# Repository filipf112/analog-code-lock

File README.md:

# Analog code lock project
Project of analog code lock with circuit and PCB design

## System assumptions and operation
The project's assumption was to construct an analog code lock. The circuit was based on the digital circuit CD4017, which operates by changing the output after each pulse at the CLK input. Eight buttons were used to create a sequence forming a password, four of which were responsible for the password, while the rest reset the circuit upon being pressed. Pressing the correct buttons in the established order activates the LED and relay RY1. To secure the circuit, diodes and resistors were used, and capacitors were installed to stabilize the current flowing in the circuit.

## Schematic
Below is the schematic of the project created in the Eagle program, along with the names and values of the components.

## Simulation
To conduct the simulation, the SimulIDE program was used. As seen, upon pressing all the buttons forming the password in the correct sequence, the LED lights up, and the relay begins to operate.

## PCB Design
Based on the schematic created in the Eagle program, the PCB layout was generated.

## Final project

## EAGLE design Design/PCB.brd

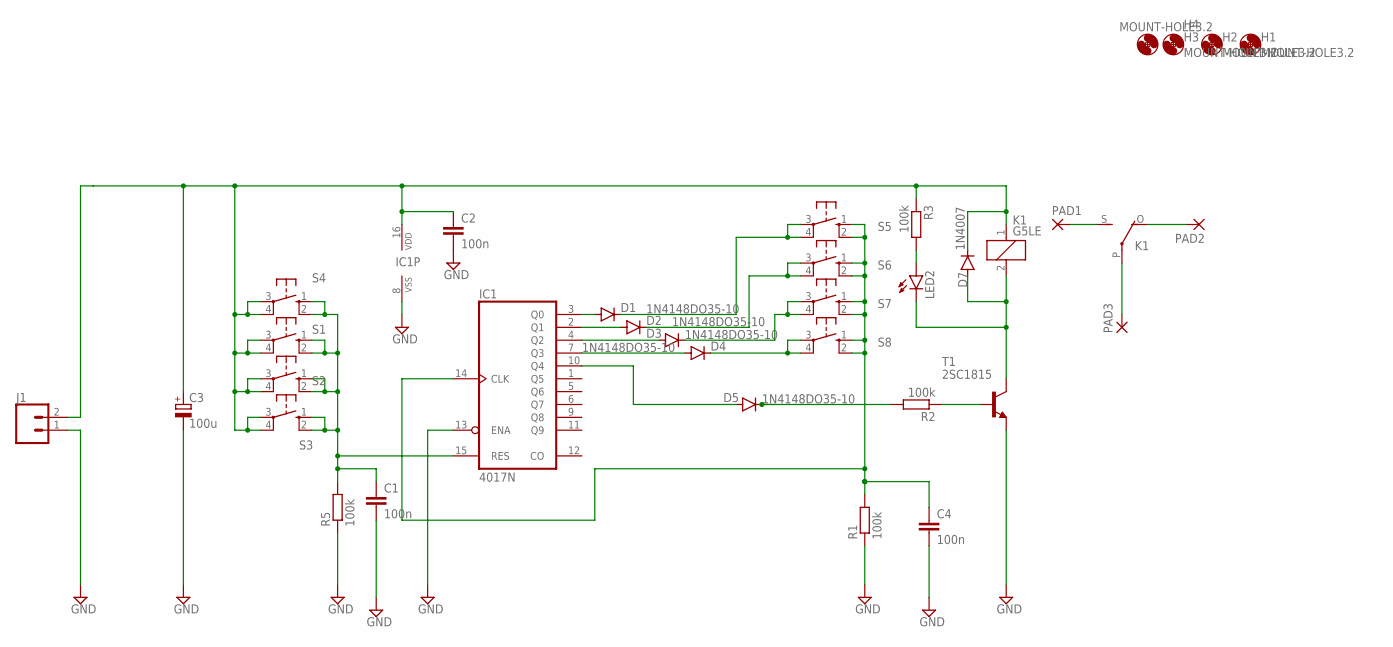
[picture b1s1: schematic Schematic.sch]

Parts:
C1, C2, C4: 100n; C025-060X050
C3: 100u; E2,5-6
D1, D2, D3, D4, D5: 1N4148DO35-10; DO35-10
D7: 1N4007; DO-41
H1, H2, H3, H4: MOUNT-HOLE3.2; 3,2
IC1: 4017N; DIL16
J1: CONN_023.5MM; SCREWTERMINAL-3.5MM-2
K1: G5LE
LED2: LED5MM
PAD1, PAD2, PAD3: 3,81/1,4
R1, R2, R3, R5: 100k; 0207/12
S1, S2, S3, S4, S5, S6, S7, S8: 10-XX; B3F-10XX
T1: 2SC1815; TO92-ECB

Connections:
GND: C1.2, C2.2, C3.-, C4.2, IC1.8 (VSS), IC1.13 (ENA), J1.1, R1.1, R5.1, T1.E
unnamed: C1.1, IC1.15 (RES), R5.2, S1.1 (S), S1.2 (S1), S2.1 (S), S2.2 (S1), S3.1 (S), S3.2 (S1), S4.1 (S), S4.2 (S1)
unnamed: D4.C, S8.3, S8.4 (P1)
unnamed: D4.A, IC1.7 (Q3)
unnamed: D3.A, IC1.4 (Q2)
unnamed: D2.A, IC1.2 (Q1)
unnamed: D1.A, IC1.3 (Q0)
unnamed: D3.C, S7.3, S7.4 (P1)
unnamed: D2.C, S6.3, S6.4 (P1)
unnamed: C4.1, IC1.14 (CLK), R1.2, S5.1 (S), S5.2 (S1), S6.1 (S), S6.2 (S1), S7.1 (S), S7.2 (S1), S8.1 (S), S8.2 (S1)
unnamed: D1.C, S5.3, S5.4 (P1)
unnamed: K1.S, PAD1.1
unnamed: D5.A, IC1.10 (Q4)
unnamed: K1.O, PAD2.1
unnamed: D7.A, K1.2, LED2.K (C), T1.C
unnamed: D5.C, R2.2
unnamed: R2.1, T1.B
unnamed: LED2.A, R3.2
unnamed: K1.P, PAD3.1
unnamed: C2.1, C3.+, D7.C, IC1.16 (VDD), J1.2, K1.1, R3.1, S1.3, S1.4 (P1), S2.3, S2.4 (P1), S3.3, S3.4 (P1), S4.3, S4.4 (P1)

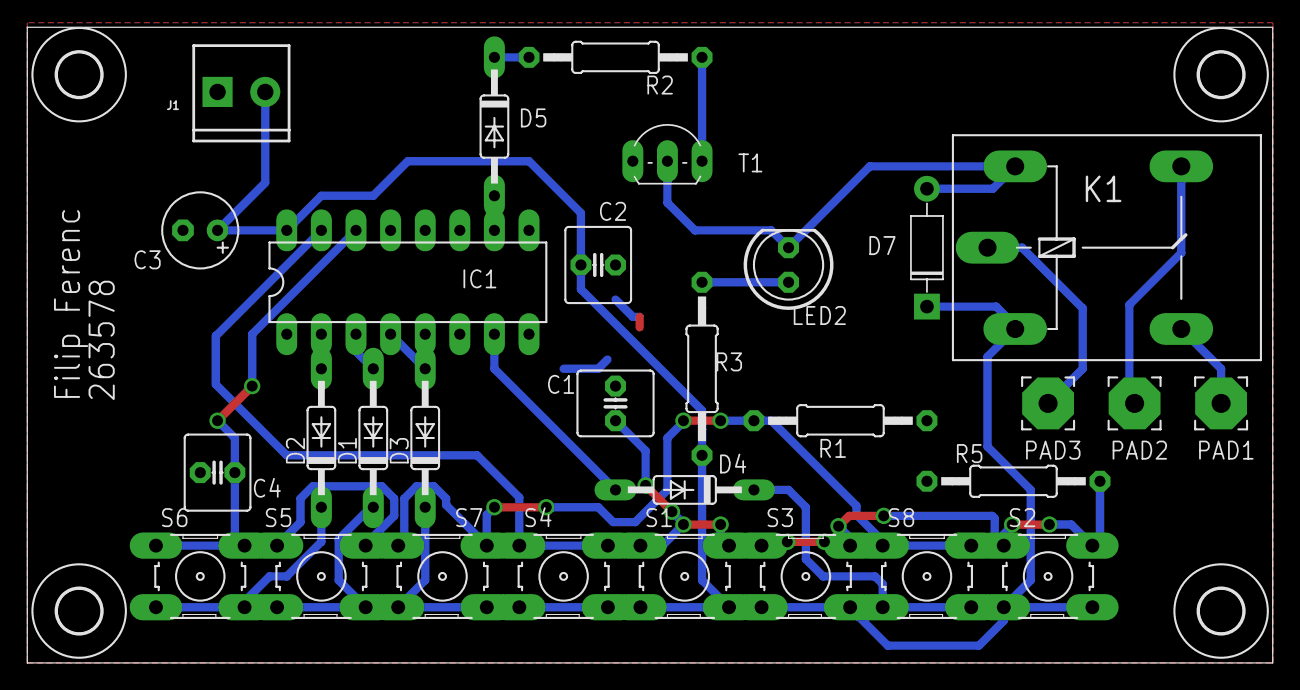
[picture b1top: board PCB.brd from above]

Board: 2 copper layers, 91.4 x 46.7 mm, 34 parts (0 on the bottom side), 20 nets.

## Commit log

2024-03-17 Adding images
2024-03-17 Final commit

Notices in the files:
parts and their libraries:
SparkFun-Connectors: Licensing: Creative Commons ShareAlike 4.0 International - https://creativecommons.org/licenses/by-sa/4.0
